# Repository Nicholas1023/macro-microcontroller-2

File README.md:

# Macro Microcontroller 2

An RP2040-based microcontroller development board with an integrated macropad which provides GPIO controls with keyboard keys on a single PCB, plus a custom BASIC interpreter and disk operating system.

Documentation page: <a href="https://nicholaslim.me/macro-microcontroller-2">https://nicholaslim.me/macro-microcontroller-2</a>

Hack Club Stardance Challenge project: <a href="https://stardance.hackclub.com/projects/21502">https://stardance.hackclub.com/projects/21502</a>

View hardware demonstration at <a href="https://nicholaslim.me/macro-microcontroller-2/assets/hardware-demo.mp4">https://nicholaslim.me/macro-microcontroller-2/assets/hardware-demo.mp4</a>!

## What's New?
1. Microcontroller unit directly soldered on board!
2. More output devices with speed and volume adjustments (Buzzer and motor).
3. More ways to power the board (Barrel jack, USB, GPIO pins).
4. Custom BASIC interpreter and a disk operating system.

## What Does it Do?
Macro Microcontroller 2 allows you to control GPIO pins using macropad-like keys and from the serial terminal using the built-in <a href="Firmware Files/macro-microcontroller-basic.c">Macro Microcontroller BASIC Interpreter</a> or a <a href="Firmware Files/macro-microcontroller-bios+dos.c">disk operating system</a> for simple uses. It offers more ways to control GPIOs by having builtin keys that can be programmed to your own needs.

## Enclosure

## Datasheet
For more details on the hardware, please read the <a href="docs/assets/macro-microcontroller-2-datasheet.pdf">datasheet</a>!

## Firmware
### Macro Microcontroller BIOS
A basic BIOS-like firmware, which performs basic POST routines and reports information on the device. <a href="Firmware Files/macro-microcontroller-bios.c">Source code</a>.
```
 _  _
| \/ | Macro Microcontroller BIOS Version 0.0.2.
|_\/_| Copyright (C) 2025-2026 Nicholas Lim.

Device: Macro Microcontroller 2 (RP2040 @ 125MHz)
Serial Number: ****************
RAM Free: 254K OK
Serial Status: Connected

Press SW1 to enter Macro Microcontroller BASIC.
Press SW2 to enter BOOTSEL mode.

Booting system...
```

### Macro Microcontroller DOS
A simple DOS-like environment that boots from the BIOS. <a href="Firmware Files/macro-microcontroller-bios+dos.c">Source code</a>.

Available commands (* denotes optional parameters):
1. `HELP`: Launches the help guide.
2. `CALCULATE`: Performs basic operations on 2 numbers. Usage: `CALCULATE [Number] [+ - * / ^ root] [Number]`
3. `ECHO`: Echoes text.
4. `PROGLIST`: Show program listing.
5. `SYSTEM`: Starts another Macro Microcontroller DOS console.
6. `EXIT`: Stops all processes for power off.
7. `OUT`: Turns on a specified GPIO for 1 second. Usage: `OUT [LED# IO# BELL MOTOR]`
8. `VERSION`: Shows the release version.
9. `BOOT`: Reboots the system. Usage: `BOOT -m [BASIC BOOTSEL]*`
10. `DEVINFO`: Displays device and memory information.
11. `UPTIME`: Shows device uptime.

### Macro Microcontroller BASIC Interpreter
A BASIC interpreter written in C for Macro Microcontroller, providing a simple coding environment via a serial terminal. You may view a demo at <a href="Assets/firmware-demo.mp4">Assets/firmware-demo.mp4</a>.

Currently available statements:
1. `PRINT`: Outputs text to the serial terminal.
2. `LET`: Assigns a value (integer, float or string) to a variable (Only one variable is allowed for now).
3. `INPUT`: Assigns a value (integer, float or string) to a variable via user input.
4. `GPIO`: Turns on a specified GPIO pin for 1 second.
5. `LSVAR`: Outputs variable name and their value to the serial terminal.
6. `END`: Clears variable and reset line numbers.
7. `EXIT`: Puts the device into sleep/power off mode.
8. `KEY`: Pass GPIO controls to the macropad.
9. `REM`: Add comments to your program.

For example programs, see <a href="Firmware Files/example.bas">Firmware Files/example.bas</a>.
Try out the web editor at <a href="https://editor.nicholaslim.me/macro-microcontroller">https://editor.nicholaslim.me/macro-microcontroller</a>!

## Schematics

View PCB file at https://kicanvas.org/?repo=https%3A%2F%2Fgithub.com%2FNicholas1023%2Fmacro-microcontroller-2%2Fblob%2Fmain%2FPCB%20Files%2Fmacro-microcontroller-2.kicad_pcb!

## Repository Structure
```
main
 ├── /docs ← Documentation website and datasheet files are here
 ├── /Assets ← Images and videos are here
 │     └── /Journal ← Images for JOURNAL.md
 ├── /PCB Files ← .kicad_ files are here
 ├── /Production Files ← Gerber and BOM files are here
 ├── /Printing Files ← STLs are here
 ├── /Firmware Files ← Firmware files are here
 ├── JOURNAL.md ← Devlogs
 ├── README.md ← This file
 ├── LICENSE.txt ← License
 └── schematics.pdf ← Schematics
 ```

## Bill of Materials (Excluding DNP)
|Component|Ref Designator|Qty|Footprint|
|---------|--------------|---|---------|
|HMB1206-03|BZ1|1|Buzzer_12x9.5RM7.6|
|Capacitor 0.1uF|C1, C2, C3, C4, C5, C6, C7, C10, C11|9|0402|
|Capacitor 8pF|C8, C9|2|0402|
|THT LED|D1, D2, D3|3|LED_D5.0mm|
|SMD LED|D4|1|0603|
|USB-B Micro Port|J1|1|USB_Micro-B_Molex_47346-0001|
|Barrel Jack|J3|1|BarrelJack_Horizontal|
|2.54 1x05 Pin|J4|1|PinHeader_1x05_P2.54mm_Vertical|
|2.54 1x02 Pin|M1|1|PinHeader_1x02_P2.54mm_Vertical|
|Resistor 27ohm|R1, R6|2|0402|
|Resistor 220ohm|R2, R4, R5, R7|4|0402|
|Resistor 5kohm|R3, R8, R9|3|0402|
|Potentiometer|RV1, RV2|2|Potentiometer_Vishay_T73YP_Vertical|
|Cherry MX Keys|SW1, SW2, SW3|3|SW_Cherry_MX_1.00u_PCB|
|Reset & Boot Button|SW4, SW6|2|SW_Push_SPST_NO_Alps_SKRK|
|DIP Switch|SW5|1|SW_DIP_SPSTx02_Slide_9.78x7.26mm_W7.62mm_P2.54mm|
|RP2040|U1|1|QFN-56-1EP_7x7mm_P0.4mm_EP3.2x3.2mm|
|TLV71311PDBVR|U2|1|SOT-23-5|
|XC6206P332MR|U3|1|SOT-23-3|
|W25Q128JVP|U4|1|WSON-8-1EP_6x5mm_P1.27mm_EP3.4x4.3mm|
|TPS76350|U6|1|SOT-23-5|
|NX3225SA-12MHz|Y1|1|Crystal_SMD_3225-4Pin_3.2x2.5mm|

## Legal
<b>Hardware files</b> ("<a href="PCB Files">PCB Files</a>", "<a href="Printing Files">Printing Files</a>", "<a href="Production Files">Production Files</a>", "<a href="schematics.pdf">schematics.pdf</a>") are licensed under the terms of the CERN-OHL-W-2.0 License from 9 September 2026 onwards. Versions prior to this date remain available under the terms of the CERN-OHL-P-2.0 License. See <a href="LICENSE.txt">LICENSE.txt</a>.

<b>Documentation files</b> ("<a href="docs">docs</a>", "<a href="Assets">Assets</a>", "<a href="JOURNAL.md">JOURNAL.md</a>") are licensed under the terms of the MIT License. See <a href="docs/LICENSE.txt">docs/LICENSE.txt</a>.

<a href="Firmware Files/macro-microcontroller-basic.c">macro-microcontroller-basic.c</a>, <a href="Firmware Files/macro-microcontroller-bios.c">macro-microcontroller-bios.c</a>, <a href="Firmware Files/macro-microcontroller-bios+dos.c">macro-microcontroller-bios+dos.c</a> are licensed under the terms of the MIT License. <a href="Firmware Files/firmware-template.c">firmware-template.c</a> is licensed under the terms of the MIT-0 License. <a href="Firmware Files/example.bas">example.bas</a> is marked <a href="https://creativecommons.org/publicdomain/zero/1.0/">CC0 1.0</a>.

Macro Microcontroller BIOS, Macro Microcontroller DOS and Macro Microcontroller BASIC compile source code from the following third-party software:

- Pico SDK: See <a href="Firmware Files/pico_sdk_import.cmake">Firmware Files/pico_sdk_import.cmake</a> for the Pico SDK license and copyright notice.

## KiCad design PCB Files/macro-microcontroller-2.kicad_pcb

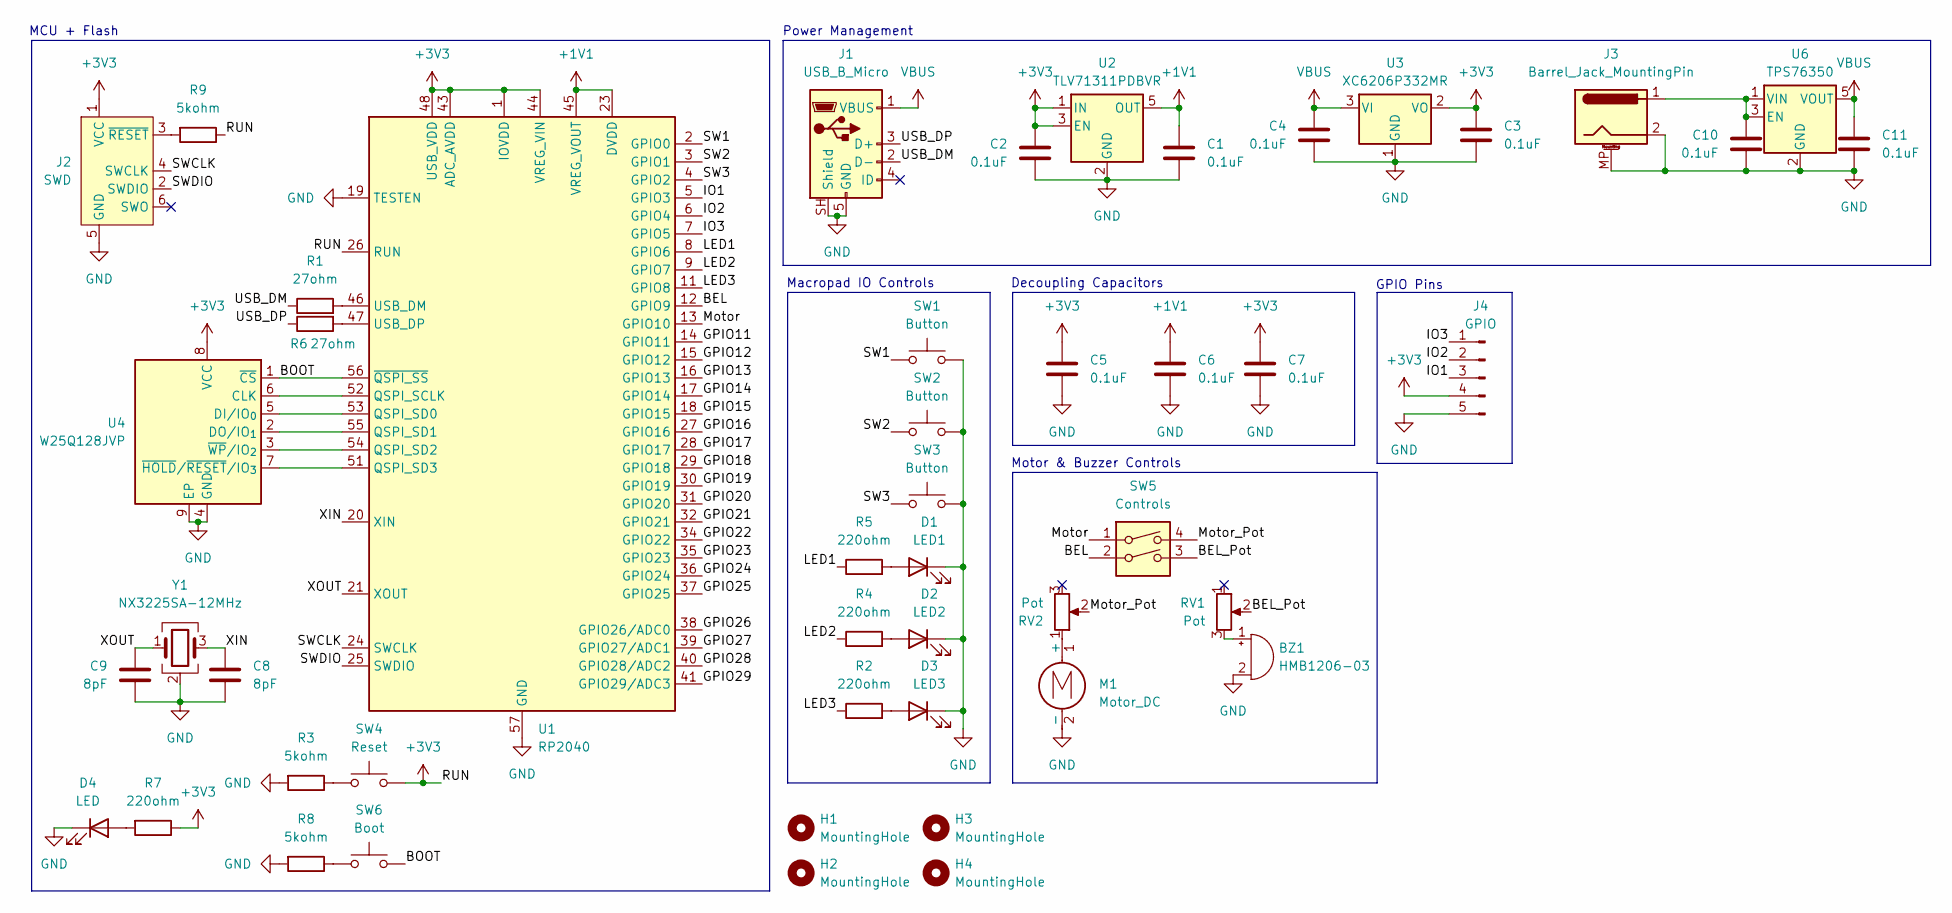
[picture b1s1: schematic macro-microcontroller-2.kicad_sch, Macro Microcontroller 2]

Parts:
BZ1: HMB1206-03; Buzzer_12x9.5RM7.6; LCSC C96101
C1, C2, C3, C4, C5, C6, C7, C10, C11: 0.1uF; C_0402_1005Metric; LCSC C1525
C8, C9: 8pF; C_0402_1005Metric; LCSC C1578
D1: LED1; LED_D5.0mm; LCSC C87271
D2: LED2; LED_D5.0mm; LCSC C87271
D3: LED3; LED_D5.0mm; LCSC C87271
D4: LED; LED_0603_1608Metric; LCSC C84266
H1, H2, H3, H4: MountingHole; MountingHole_2.5mm
J1: USB_B_Micro; USB_Micro-B_Molex_47346-0001; LCSC C132560
J2: SWD; Tag-Connect_TC2030-IDC-NL_2x03_P1.27mm_Vertical
J3: Barrel_Jack_MountingPin; BarrelJack_Horizontal; LCSC C16214
J4: GPIO; PinHeader_1x05_P2.54mm_Vertical; LCSC C5156614
M1: Motor_DC; PinHeader_1x02_P2.54mm_Vertical; LCSC C2905434
R1, R6: 27ohm; R_0402_1005Metric; LCSC C25156
R2, R4, R5, R7: 220ohm; R_0402_1005Metric; LCSC C25091
R3, R8, R9: 5kohm; R_0402_1005Metric; LCSC C5948099
RV1, RV2: Pot; Potentiometer_Vishay_T73YP_Vertical; LCSC C6278770
SW1, SW2, SW3: Button; SW_Cherry_MX_1.00u_PCB
SW4: Reset; SW_Push_SPST_NO_Alps_SKRK; LCSC C115357
SW5: Controls; SW_DIP_SPSTx02_Slide_9.78x7.26mm_W7.62mm_P2.54mm; LCSC C92646
SW6: Boot; SW_Push_SPST_NO_Alps_SKRK; LCSC C115357
U1: RP2040; QFN-56-1EP_7x7mm_P0.4mm_EP3.2x3.2mm; LCSC C2040
U2: TLV71311PDBVR; SOT-23-5; LCSC C205964
U3: XC6206P332MR; SOT-23-3; LCSC C5148692
U4: W25Q128JVP; WSON-8-1EP_6x5mm_P1.27mm_EP3.4x4.3mm; LCSC C190862
U6: TPS76350; SOT-23-5; LCSC C194609
Y1: NX3225SA-12MHz; Crystal_SMD_3225-4Pin_3.2x2.5mm; LCSC C481400

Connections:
+1V1: C1.1, C6.1, U1.23 (DVDD), U1.45 (VREG_VOUT), U1.50 (DVDD), U2.5 (OUT)
+3V3: C2.1, C3.1, C5.1, C7.1, J2.1 (VCC), J4.4, R7.1, R9.1, SW4.2, U1.1 (IOVDD), U1.10 (IOVDD), U1.22 (IOVDD), U1.26 (RUN), U1.33 (IOVDD), U1.42 (IOVDD), U1.43 (ADC_AVDD), U1.44 (VREG_VIN), U1.48 (USB_VDD), U1.49 (IOVDD), U2.1 (IN), U2.3 (EN), U3.2 (VO), U4.8 (VCC)
/BEL: SW5.2, U1.12 (GPIO9)
/BEL_Pot: RV1.2, SW5.3
/BOOT: SW6.2, U1.56 (~QSPI_SS), U4.1 (~CS)
/GPIO11: U1.14 (GPIO11)
/GPIO12: U1.15 (GPIO12)
/GPIO13: U1.16 (GPIO13)
/GPIO14: U1.17 (GPIO14)
/GPIO15: U1.18 (GPIO15)
/GPIO16: U1.27 (GPIO16)
/GPIO17: U1.28 (GPIO17)
/GPIO18: U1.29 (GPIO18)
/GPIO19: U1.30 (GPIO19)
/GPIO20: U1.31 (GPIO20)
/GPIO21: U1.32 (GPIO21)
/GPIO22: U1.34 (GPIO22)
/GPIO23: U1.35 (GPIO23)
/GPIO24: U1.36 (GPIO24)
/GPIO25: U1.37 (GPIO25)
/GPIO26: U1.38 (GPIO26/ADC0)
/GPIO27: U1.39 (GPIO27/ADC1)
/GPIO28: U1.40 (GPIO28/ADC2)
/GPIO29: U1.41 (GPIO29/ADC3)
/IO1: J4.3, U1.5 (GPIO3)
/IO2: J4.2, U1.6 (GPIO4)
/IO3: J4.1, U1.7 (GPIO5)
/LED1: R5.1, U1.8 (GPIO6)
/LED2: R4.1, U1.9 (GPIO7)
/LED3: R2.1, U1.11 (GPIO8)
/Motor: SW5.1, U1.13 (GPIO10)
/Motor_Pot: RV2.2, SW5.4
/SW1: SW1.1, U1.2 (GPIO0)
/SW2: SW2.1, U1.3 (GPIO1)
/SW3: SW3.1, U1.4 (GPIO2)
/SWCLK: J2.4 (SWCLK), U1.24 (SWCLK)
/SWDIO: J2.2 (SWDIO), U1.25 (SWDIO)
/USB_DM: J1.2 (D-), R1.1
/USB_DP: J1.3 (D+), R6.1
/XIN: C8.1, U1.20 (XIN), Y1.3
/XOUT: C9.1, U1.21 (XOUT), Y1.1
GND: BZ1.2 (-), C1.2, C2.2, C3.2, C4.2, C5.2, C6.2, C7.2, C8.2, C9.2, C10.2, C11.2, D1.1 (K), D2.1 (K), D3.1 (K), D4.1 (K), J1.5 (GND), J1.SH (Shield), J2.5 (GND), J3.2, J3.MP (MountPin), J4.5, M1.2 (-), R3.2, R8.2, SW1.2, SW2.2, SW3.2, U1.19 (TESTEN), U1.57 (GND), U2.2 (GND), U3.1 (GND), U4.4 (GND), U4.9 (EP), U6.2 (GND), Y1.2 (G), Y1.4 (G)
unnamed: BZ1.1 (+), RV1.3
unnamed: D1.2 (A), R5.2
unnamed: D2.2 (A), R4.2
unnamed: D3.2 (A), R2.2
unnamed: D4.2 (A), R7.2
unnamed: J2.3 (~RESET), R9.2
unnamed: M1.1 (+), RV2.1
unnamed: R3.1, SW4.1
unnamed: R8.1, SW6.1
unnamed: U1.52 (QSPI_SCLK), U4.6 (CLK)
unnamed: U1.53 (QSPI_SD0), U4.5 (DI/IO_{0})
unnamed: U1.55 (QSPI_SD1), U4.2 (DO/IO_{1})
unnamed: U1.54 (QSPI_SD2), U4.3 (~WP/IO_{2})
unnamed: U1.51 (QSPI_SD3), U4.7 (~HOLD/~RESET/IO_{3})
unnamed: R1.2, U1.46 (USB_DM)
unnamed: R6.2, U1.47 (USB_DP)
unnamed: C10.1, J3.1, U6.1 (VIN), U6.3 (EN)
VBUS: C4.1, C11.1, J1.1 (VBUS), U3.3 (VI), U6.5 (VOUT)

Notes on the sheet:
Macropad IO Controls
GPIO Pins
Power Management
Decoupling Capacitors
MCU + Flash
Motor & Buzzer Controls

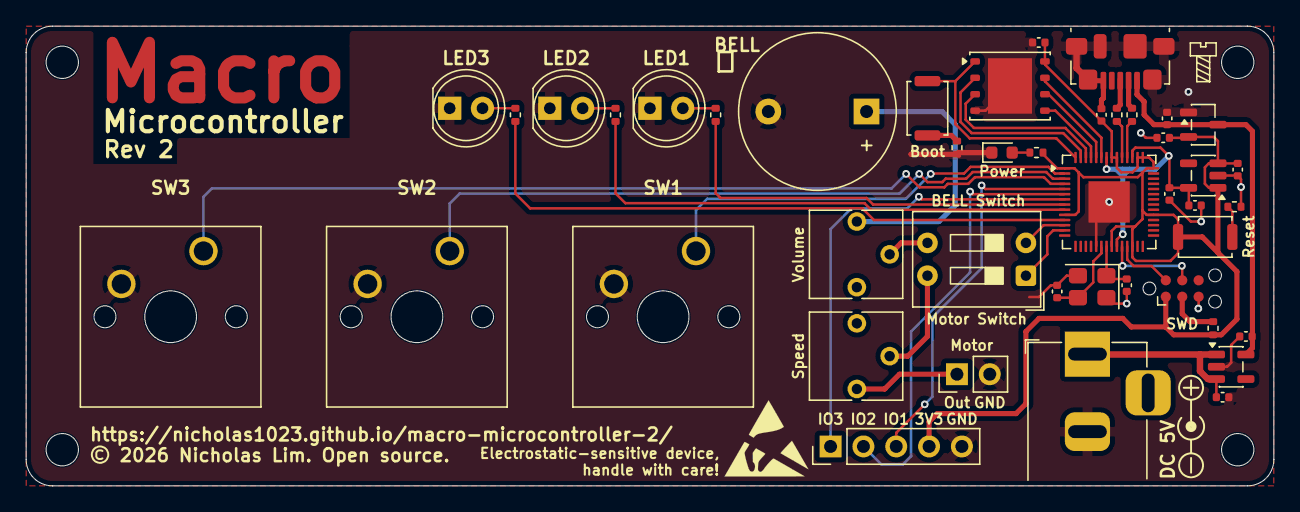
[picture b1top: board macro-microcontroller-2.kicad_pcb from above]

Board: 2 copper layers, 96.5 x 35.6 mm, 48 parts (0 on the bottom side), 41 nets.

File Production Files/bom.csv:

Designator,Footprint,Quantity,Value,LCSC Part #
BZ1,Buzzer_12x9.5RM7.6,1,HMB1206-03,C96101
"C1, C10, C11, C2, C3, C4, C5, C6, C7",0402,9,0.1uF,C1525
"C8, C9",0402,2,8pF,C1578
D1,LED_D5.0mm,1,LED1,C87271
D2,LED_D5.0mm,1,LED2,C87271
D3,LED_D5.0mm,1,LED3,C87271
D4,0603,1,LED,C84266
J1,USB_Micro-B_Molex_47346-0001,1,USB_B_Micro,C132560
J3,BarrelJack_Horizontal,1,Barrel_Jack_MountingPin,C16214
J4,PinHeader_1x05_P2.54mm_Vertical,1,GPIO,C5156614
M1,PinHeader_1x02_P2.54mm_Vertical,1,Motor_DC,C2905434
"R1, R6",0402,2,27ohm,C25156
"R2, R4, R5, R7",0402,4,220ohm,C25091
"R3, R8, R9",0402,3,5kohm,C5948099
"RV1, RV2",Potentiometer_Vishay_T73YP_Vertical,2,Pot,C6278770
"SW1, SW2, SW3",SW_Cherry_MX_1.00u_PCB,3,Button,
SW4,SW_Push_SPST_NO_Alps_SKRK,1,Reset,C115357
SW5,SW_DIP_SPSTx02_Slide_9.78x7.26mm_W7.62mm_P2.54mm,1,Controls,C92646
SW6,SW_Push_SPST_NO_Alps_SKRK,1,Boot,C115357
U1,QFN-56-1EP_7x7mm_P0.4mm_EP3.2x3.2mm,1,RP2040,C2040
U2,SOT-23-5,1,TLV71311PDBVR,C205964
U3,SOT-23-3,1,XC6206P332MR,C5148692
U4,WSON-8-1EP_6x5mm_P1.27mm_EP3.4x4.3mm,1,W25Q128JVP,C190862
U6,SOT-23-5,1,TPS76350,C194609
Y1,Crystal_SMD_3225-4Pin_3.2x2.5mm,1,NX3225SA-12MHz,C481400

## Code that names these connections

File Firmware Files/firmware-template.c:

// SPDX-License-Identifier: MIT-0
// Macro Microcontroller 2 Custom Firmware Template
// This template assigns GPIO pins to built-in IO devices and set pin mode.
/*
MIT No Attribution

Copyright (C) 2026 Nicholas Lim.

Permission is hereby granted, free of charge, to any person obtaining a copy
of this software and associated documentation files (the "Software"), to deal
in the Software without restriction, including without limitation the rights
to use, copy, modify, merge, publish, distribute, sublicense, and/or sell
copies of the Software, and to permit persons to whom the Software is
furnished to do so.

THE SOFTWARE IS PROVIDED "AS IS", WITHOUT WARRANTY OF ANY KIND, EXPRESS OR
IMPLIED, INCLUDING BUT NOT LIMITED TO THE WARRANTIES OF MERCHANTABILITY,
FITNESS FOR A PARTICULAR PURPOSE AND NONINFRINGEMENT. IN NO EVENT SHALL THE
AUTHORS OR COPYRIGHT HOLDERS BE LIABLE FOR ANY CLAIM, DAMAGES OR OTHER
LIABILITY, WHETHER IN AN ACTION OF CONTRACT, TORT OR OTHERWISE, ARISING FROM,
OUT OF OR IN CONNECTION WITH THE SOFTWARE OR THE USE OR OTHER DEALINGS IN THE
SOFTWARE.
*/

#include <stdio.h>
#include "pico/stdlib.h"
#include "pico/sync.h"

void userProgram();

// By default, IO pins are set to output mode.
int IOMode = 0;
// Uncomment the following line to set IO pins to input mode.
// int IOMode = 1;

// Assign GPIOs to switches.
const int SW1 = 0;
const int SW2 = 1;
const int SW3 = 2;

// Assign GPIOs to pins.
const int IO1 = 3;
const int IO2 = 4;
const int IO3 = 5;

// Assign GPIOs to LEDs.
const int LED1 = 6;
const int LED2 = 7;
const int LED3 = 8;

// Assign GPIOs to buzzer and motor.
const int BELL = 9;
const int MOTOR = 10;

void main() {
    // GPIO initialisation and mode setting.
    stdio_init_all();
    gpio_init(SW1);
    gpio_init(SW2);
    gpio_init(SW3);
    gpio_init(IO1);
    gpio_init(IO2);
    gpio_init(IO3);
    gpio_init(LED1);
    gpio_init(LED2);
    gpio_init(LED3);
    gpio_init(BELL);
    gpio_init(MOTOR);
    gpio_set_dir(SW1, GPIO_IN);
    gpio_set_dir(SW2, GPIO_IN);
    gpio_set_dir(SW3, GPIO_IN);
    gpio_set_dir(LED1, GPIO_OUT);
    gpio_set_dir(LED2, GPIO_OUT);
    gpio_set_dir(LED3, GPIO_OUT);
    gpio_set_dir(BELL, GPIO_OUT);
    gpio_set_dir(MOTOR, GPIO_OUT);
    if (IOMode == 0) {
        gpio_set_dir(IO1, GPIO_OUT);
        gpio_set_dir(IO2, GPIO_OUT);
        gpio_set_dir(IO3, GPIO_OUT);
    } else if (IOMode == 1) {
        gpio_set_dir(IO1, GPIO_IN);
        gpio_set_dir(IO2, GPIO_IN);
        gpio_set_dir(IO3, GPIO_IN);
    }
    userProgram();
    while (1) __wfi(); // Set MCU to sleep mode.
}

void userProgram() {
    // Write your code here!
}

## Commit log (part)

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2026-06-20 Upload files
2026-06-20 Update firmware
2026-06-20 Update enclosure for barrel jack
2026-06-21 Add JOURNAL.md and assets
2026-06-21 Update components
2026-06-21 Update schematics
2026-06-23 Add documentation website
2026-06-23 Rename folder
2026-06-23 Update journal
2026-06-23 Update website to be responsive
2026-06-24 Update documentation
2026-06-24 Minor updates to docs
2026-06-24 Edit "firmware" section
2026-06-24 Edit "firmware" section again
2026-06-24 Update PCB
2026-06-24 Update images
2026-06-24 Edit index.html
2026-06-25 Add favicon.ico
2026-06-26 Update docs
2026-06-26 Add SDK import file
2026-06-26 Update production files
2026-06-26 Edit repo structure

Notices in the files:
PCB Files/macro-microcontroller-2.kicad_pcb:
Designed by Nicholas Lim. Open source under the CERN-OHL-W-2.0 License.
